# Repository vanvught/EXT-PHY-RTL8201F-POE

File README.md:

# External PHY RTL8201F with POE

Successfully tested with [https://www.adafruit.com/product/3847](https://www.adafruit.com/product/3847)

More information [https://www.gd32-dmx.org/ethernet.html](https://www.gd32-dmx.org/ethernet.html)

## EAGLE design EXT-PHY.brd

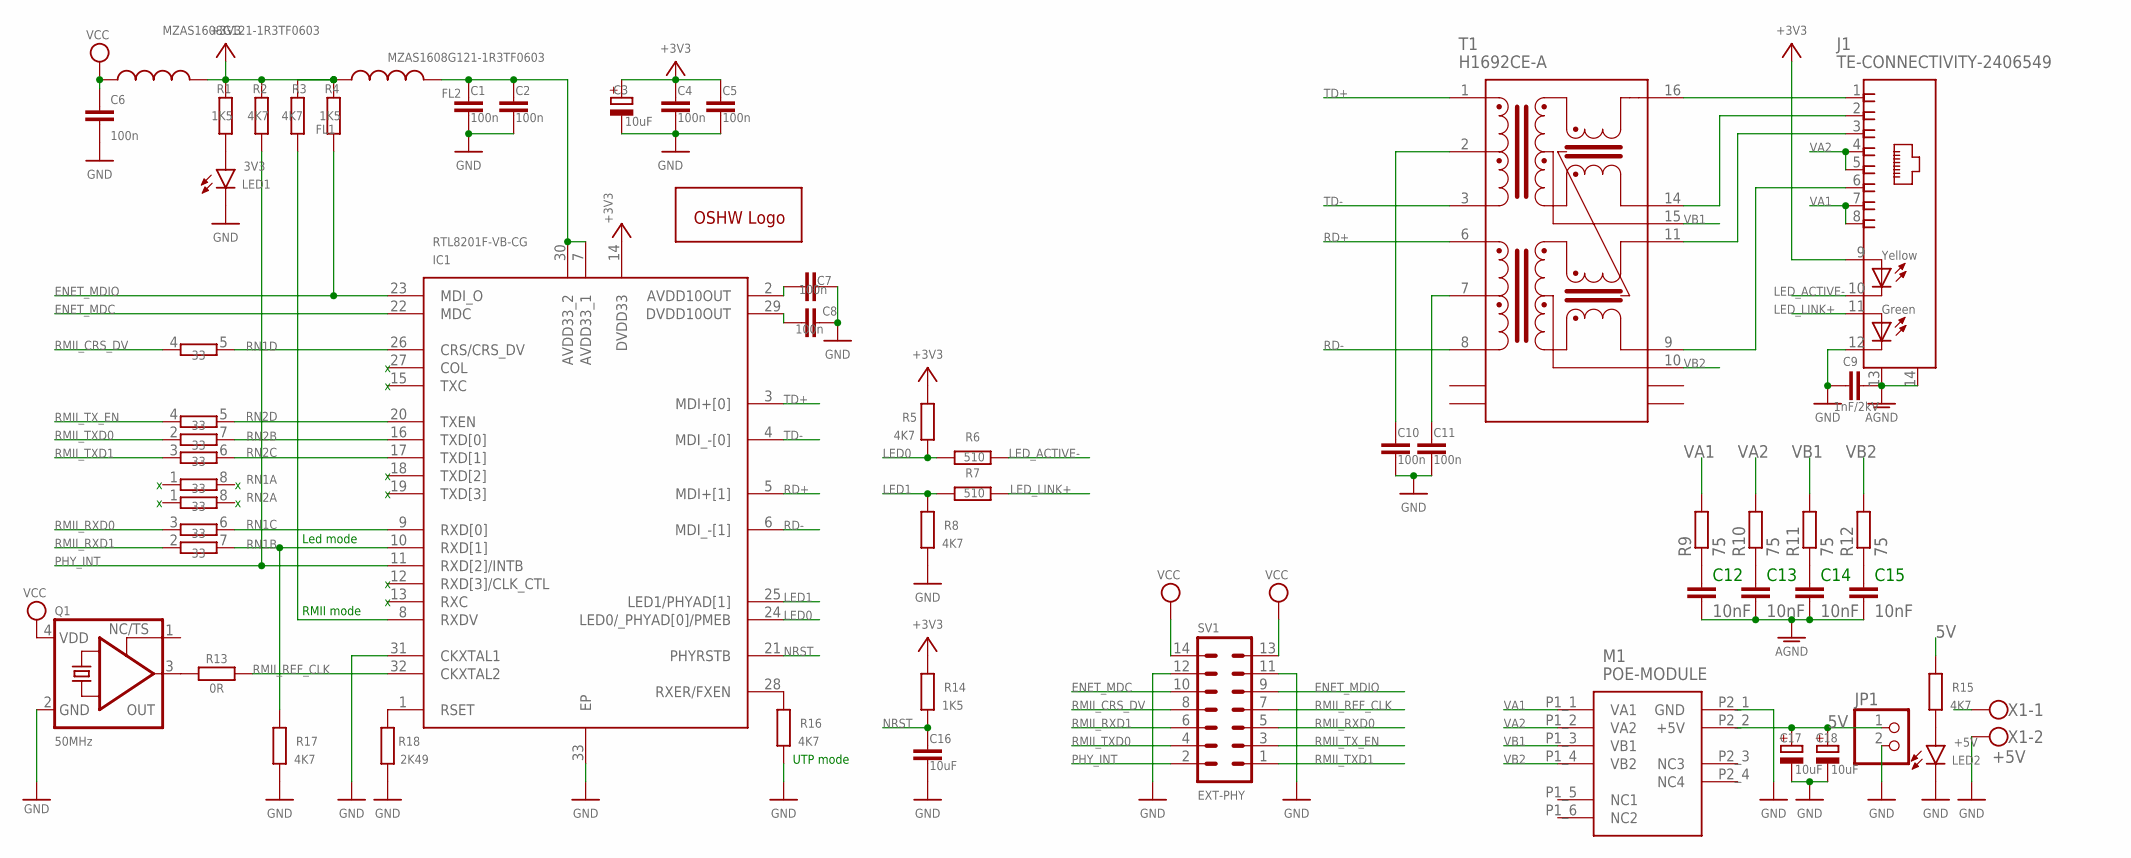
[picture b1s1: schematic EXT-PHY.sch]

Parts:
C1, C2, C4, C5, C6, C7, C8, C10, C11: 100n; C0603; JLCPCB C14663
C3, C17, C18: 10uF; A/3216-18R; JLCPCB C7171
C9: 1nF/2kV; C1206; JLCPCB C9196
C12, C13, C14, C15: 10nF; C0805; JLCPCB C106844
C16: 10uF; C0603; JLCPCB C19702
FL1, FL2: MZAS1608G121-1R3TF0603; 0603
GOLD_ORB_SM1: OSHWLOGOLOGO5MM; OSHW_5MM
IC1: RTL8201F-VB-CG; QFN50P500X500X100-33N; JLCPCB C45044
J1: TE-CONNECTIVITY-2406549; 34065493
JP1: PINHD-1X2; 1X02
LED1: 3V3; CHIP-LED0603; JLCPCB C72043
LED2: +5V; CHIP-LED0603; JLCPCB C72043
M1: POE-MODULE
Q1: 50MHz; 3.2X2.5_KXO-V96; JLCPCB C160451
R1, R4, R14: 1K5; R0603; JLCPCB C22843
R2, R3, R5, R8, R15, R16, R17: 4K7; R0603; JLCPCB C23162
R6, R7: 510; R0603; JLCPCB C23193
R9, R10, R11, R12: 75; R0603; JLCPCB C228048
R13: 0R; R0603; JLCPCB C115304
R18: 2K49; R0603; JLCPCB C100897
RN1, RN2: 33; 4X0402ARV341; JLCPCB C25501
SV1: EXT-PHY; MA07-2W
T1: H1692CE-A; SOIC127P952X572-16N
X1: +5V; W237-102

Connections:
5V: C17.+, C18.+, JP1.1, M1.P2_2 (+5V), R15.2, X1.1
50MHZ: Q1.3 (OUT), R13.1
+3V3: C3.+, C4.1, C5.1, FL1.2, FL2.1, IC1.14 (DVDD33), J1.9 (+_1), R1.2, R2.2, R3.1, R4.2, R5.2, R14.2
AGND: C9.2, C12.2, C13.2, C14.2, C15.2, J1.13 (S1), J1.14 (S2)
AVDD: C1.1, C2.1, FL2.2, IC1.7 (AVDD33_1), IC1.30 (AVDD33_2)
ENET_MDC: IC1.22 (MDC), SV1.10
ENET_MDIO: IC1.23 (MDI_O), R4.1, SV1.9
GND: C1.2, C2.2, C3.-, C4.2, C5.2, C6.2, C7.2, C8.1, C9.1, C10.2, C11.2, C16.2, C17.-, C18.-, IC1.31 (CKXTAL1), IC1.33 (EP), J1.12 (-_2), JP1.2, LED1.C, LED2.C, M1.P2_1 (GND), Q1.2 (GND), R8.1, R16.1, R17.1, R18.2, SV1.11, SV1.12, X1.2
LED0: IC1.24 (LED0/_PHYAD[0]/PMEB), R5.1, R6.2
LED1: IC1.25 (LED1/PHYAD[1]), R7.2, R8.2
LED_ACTIVE-: J1.10 (-_1), R6.1
LED_LINK+: J1.11 (+_2), R7.1
unnamed: LED1.A, R1.1
unnamed: LED2.A, R15.1
unnamed: C10.1, T1.2
unnamed: IC1.1 (RSET), R18.1
unnamed: IC1.8 (RXDV), R3.2
unnamed: C8.2, IC1.29 (DVDD10OUT)
unnamed: IC1.28 (RXER/FXEN), R16.2
unnamed: J1.1, T1.16
unnamed: C12.1, R9.1
unnamed: C13.1, R10.1
unnamed: C7.1, IC1.2 (AVDD10OUT)
unnamed: J1.2, T1.14
unnamed: J1.3, T1.11
unnamed: J1.6, T1.9
unnamed: C11.1, T1.7
unnamed: C14.1, R11.1
unnamed: C15.1, R12.1
NRST: C16.1, IC1.21 (PHYRSTB), R14.1
PHY_INT: IC1.11 (RXD[2]/INTB), R2.1, SV1.2
RD+: IC1.5 (MDI+[1]), T1.6
RD-: IC1.6 (MDI_-[1]), T1.8
RMII_CRS_DV: RN1.4 (1), SV1.8
RMII_REF_CLK: IC1.32 (CKXTAL2), R13.2, SV1.7
RMII_RXD0: RN1.3 (1), SV1.5
RMII_RXD1: RN1.2 (1), SV1.6
RMII_TXD0: RN2.2 (1), SV1.4
RMII_TXD1: RN2.3 (1), SV1.1
RMII_TX_EN: RN2.4 (1), SV1.3
RXD0: IC1.9 (RXD[0]), RN1.6 (2)
RXD1: IC1.10 (RXD[1]), R17.2, RN1.7 (2)
RXDV: IC1.26 (CRS/CRS_DV), RN1.5 (2)
TD+: IC1.3 (MDI+[0]), T1.1
TD-: IC1.4 (MDI_-[0]), T1.3
TXD0: IC1.16 (TXD[0]), RN2.7 (2)
TXD1: IC1.17 (TXD[1]), RN2.6 (2)
TXEN: IC1.20 (TXEN), RN2.5 (2)
VA1: J1.7, J1.8, M1.P1_1 (VA1), R9.2
VA2: J1.4, J1.5, M1.P1_2 (VA2), R10.2
VB1: M1.P1_3 (VB1), R11.2, T1.15
VB2: M1.P1_4 (VB2), R12.2, T1.10
VCC: C6.1, FL1.1, Q1.4 (VDD), SV1.13, SV1.14

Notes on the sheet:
RMII mode
UTP mode
Led mode

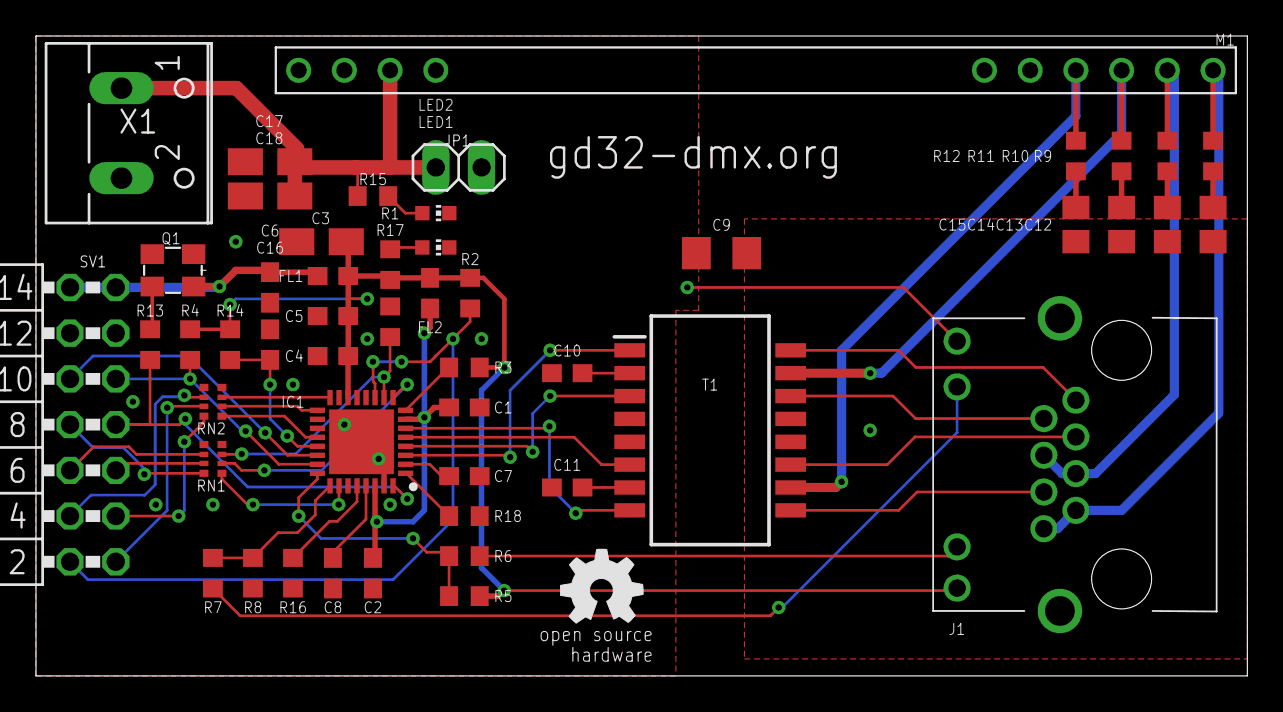
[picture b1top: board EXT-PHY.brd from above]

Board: 2 copper layers, 67.3 x 35.6 mm, 51 parts (0 on the bottom side), 53 nets.

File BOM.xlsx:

Qty | Designator | Footprint | Comment | LCSC Part #
9 | C1, C2, C4, C5, C6, C7, C8, C10, C11 | C0603 | 100n | C14663
4 | C12, C13, C14, C15 | C0805 | 10nF | C106844
1 | C16 | C0603 | 10uF | C19702
3 | C3, C17, C18 | A/3216-18R | 10uF | C7171
1 | C9 | C1206 | 1nF/2kV | C9196
2 | FL1, FL2 | 603 | MZAS1608G121-1R3TF0603 | C709642
1 | IC1 | QFN50P500X500X100-33N | RTL8201F-VB-CG | C45044
1 | J1 | 34065493 | TE-CONNECTIVITY-2406549 | C125068
2 | LED1, LED2 | CHIP-LED0603 | 3V3 | C2286
1 | Q1 | 3.2X2.5_KXO-V96 | 50MHz | C160451
3 | R1, R4, R14 | R0603 | 1K5 | C22843
1 | R13 | R0603 | 0R | C2889381
1 | R18 | R0603 | 2K49 | C100897
7 | R2, R3, R5, R8, R15, R16, R17 | R0603 | 4K7 | C23162
2 | R6, R7 | R0603 | 510 | C23193
4 | R9, R10, R11, R12 | R0603 | 75 | C228048
2 | RN1, RN2 | 4X0402ARV341 | 33 | C25501
1 | T1 | SOIC127P952X572-16N | H1692CE-A | C2904705

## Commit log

2026-03-12 Add EXT-PHY PCB files, BOM/CPL and Gerbers
2026-03-12 Add funding file and update README
    Add .github/FUNDING.yml with a custom PayPal funding URL. Update README title to a more readable form and append an additional reference link to GD32-DMX Ethernet documentation while preserving the A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

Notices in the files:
parts and their libraries:
crystal-geyer_V1_0: Copyright: Geyer-Electronic
